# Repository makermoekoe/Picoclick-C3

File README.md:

# Picoclick-C3

</a>
</a>

The Picoclick C3 as well as its little brother (the C3T, T = tiny) are the successors of the well known [Picoclick](https://github.com/makermoekoe/Picoclick). The name is related to its new processor: the [ESP32-C3](https://www.espressif.com/sites/default/files/documentation/esp32-c3_datasheet_en.pdf) single core RISC-V 160MHz CPU.

The Picoclick is a tiny WiFi and BLE IoT button for several applications. Originally designed for smart home things, the Picoclick can also be used as an actuator for IFTTT automations or as an MQTT device. It is based on the single core ESP32-C3 RISC-V processor and therefore comes with tons of useful features.
With dimensions of only 10.5mm by 18mm, the C3T is not only the smallest one in the family of the Picoclicks, it is also the smallest device I have created so far.

The [Youtube video of the C3T](https://www.youtube.com/watch?v=t-50w3RsUlg) shows the assembly and soldering process, the optimization of the boot up time, the power measurements as well as some useful applications of the Picoclick.

Here are some specs of the Picoclick C3T:
- Dimensions are only 10.5x18mm
- Ultra low standby current due to latching circuit (no sleep mode needed)
- Single button & LED interface (WS2812 RGB LED)
- USB Type-C for charging the battery and flashing the ESP32-C3

## Update 14.07.2022: The Picoclick C3 is alive!

It's a pleasure for me to announce that the Picoclick C3 (the big brother of the C3T) is finally here! It comes with the most advanced features of my latest projects which occupies the following points:

- Optimized idle current: we're below 200nA (!!) current consumption (without battery protection) in idle state! (compared to 3µA for the C3T)
- Optimized antenna design, which will lead to a better performance and longer range.
- Optimized power latching circuit, which makes the firmware development easier. (especially with the Arduino IDE)
- Optimized battery charging circuit with separated status LED.
- Added second RTC crystal.
- Added FPC connector for connecting external hardware.
- Added embedded battery protection.
- Added boot emergency jumper.
- Same dimensions as the standard Picoclick.
- Added a nice "golden" logo ;)

### [Main documentation of the Picoclick-C3 can be found here!](https://makermoekoe.gitbook.io/picoclick-c3/)

## GPIOs

Function | GPIO C3T | GPIO C3 | Mode
-------- | -------- | -------- | --------
LED | GPIO6 | GPIO6 (CLK) + GPIO7 (SDI) | Output
Latch* | GPIO3 | ** | Output
Button | GPIO5 | GPIO5 | Input
Charge Stat. | GPIO1  | ext. LED | Input
Bat Voltage | GPIO4 | GPIO4 | Input
Bat Voltage EN | -- | GPIO3 | Output

*Enabling the LDO can be done by pressing the button of the device or turning the latch high. In most use cases, the latch GPIO should be turned on as the first task of the Picoclick. Once the task is completed the device can be powered off by turning the latch off (e.g. pulling it low).

**The Picoclick C3 doesn't need a latching GPIO because it uses the embedded flash's power supply pin as a reference. It can be depowered with putting the ESP32 in deepsleep. To reduce the power consumption of the ESP32 this function will disable the power of the embedded flash (`VDD_SPI`) which in result will depower the Picoclick itself. The deepsleep calling function is only necessary to pulling the `VDD_SPI` line low, not to use the deepsleep mode of the ESP32.

## Reducing power consumption

In order to reduce the power consumption of the Picoclick the following points can be done:

- Disable WiFi while not in use (e.g. if using LED animations only): `WiFi.mode(WIFI_OFF);`
- Reducing CPU frequency after WiFi stuff is completed (crystal is 40MHz): `setCpuFrequencyMhz(10); //reduce to 10MHz`
- Reducing brightness of the LEDs (can be done right after FastLED init): `FastLED.setBrightness(150);`

## Board overview C3T (Battery connections)

</a>

## Flashing firmware to the ESP32 (C3T)

**- Press and hold the button during the complete flashing process! Otherwise the ESP32 will be loose power and the upload process will crash!**

**- A battery or a power supply has to be applied to the battery pads (3.5v - 5.5v) in order to flash the device!**

Except the above, the Picoclick behaves like a normal development board. No need to get the ESP32 into download mode or pressing any reset button.

## Speed up boot process

**Following instructions are only needed for the C3T, not for the C3 as it doesn't use a separate latching GPIO.**

Due to the latching circuit, the button press has to be longer than the boot up time of the processor, because the first task should have been executed once the button is released. For most of the use cases of the Picoclick the first task is to toggle the latch GPIO high in order to enable power hold feature of the Picoclick. If this task haven't been executed before the button is released, the Picoclick is going to standby mode without finishing its main task.
Standard boot up time of the ESP32-C3 is almost 300ms. So the first task will be executed after these 300ms. This is far too long because a standard button press (especially with the metal buttons on the C3T) is around 100ms-200ms or even slightly below. Almost every task of the Picoclick would have been interrupted in this case (unless you press and hold the button...).
To speed up the boot process I got familiar with the ```menuconfig``` of the ESP-IDF. Actually the reason why I've switched from the Arduino framework to ESP-IDF was that I get access to all the configs of the ESP32-C3.

Things I have done so far:
- Set *Flash SPI mode* from *DIO* to *QIO* (in Serial flasher config)
- Set *Log output* from *Info* to *Warning* (in component config)
- Set *Bootloader log verbosity* from *Info* to *Warning* (in Bootloader config)
- Enable *Skip image validation from power on* (in Bootloader config)

These points result in a boot up time of around 68ms which is almost quite fantastic. The test I've done so far were quite sufficient. If it is possible to make it even faster or if you have other ideas which could lead into the right direction then please let me know!

## Power consumption C3T

These power measurements are done with the Otii Arc power analyzer and its dedicated software. The average and peak current can be seen in the top right corner and is based on the selected frame in the current graph.
The Picoclick C3T is used as an ESP-NOW slave in this case, which is probably the fastest solution of any wireless connection.

A complete Picoclick task will look like this, whereby the LED part in the end is the longest part. The whole task took about 1,7 seconds, but the transmission itself is completed after around 200ms. The other part is with disabled WiFi and only used to do some visualizations with the LED. Overall average current is below 28mA.

</a>

The ESP-NOW package is sent in the first 200ms. Average current is 73mA here.

</a>

As already said, the rest is just visualization stuff which will use 22mA of current in average.

</a>

Probably the most interesting part is the standby current, because it's the most used state of the Picoclick. As the device doesn't use any sleep mode, we're getting as low as 3µA in this state. This is only related to the battery monitoring feature. As the voltage divider between ```Vbat``` and ```GND``` is ```1MOhm + 250kOhm = 1.25MOhm``` the current flow through it is about 3µA.

</a>

## Battery for the Picoclick

### C3T

The optimal battery, which is shown in the picture below, is a 301012 LiPo battery (3.0mm thick, 10mm width, 12mm length). Nevertheless you can use whatever single cell LiPo battery you want. Charging current is set to 20mA, to be used with those 20-30mAh batteries. For larger capacity batteries the battery charging time will - of course - increase. For 20-30mAh charging time is about 1h - 1,5h.

Below are some links for those tiny batteries (no sponsor, no affiliate, just for info):

[Aliexpress 301012](https://de.aliexpress.com/item/1005003644834180.html)

[Aliexpress 401012](https://de.aliexpress.com/item/32794940086.html)

[eBay 301012](https://www.ebay.com/itm/333907143841)

</a>

### C3

As the Picoclick C3 comes with an embedded battery protection, the protection of the LiPo battery itself is redundant. Therefore you can use these tiny cells which are used by BT headsets. They come in a 401010 or 301010 package.

[Aliexpress 401010](https://de.aliexpress.com/item/1005004324462178.html)

## Flashing adapter with pogopins for the C3T

In order to flash boards without soldering wires or batteries to the Picoclick, I decided to print a simple flashing adapter which uses 1mm pogopins to make contact to the battery pads on the board. Just plug in the USB cable, shift the device in, press it down to the pogopins and hit the upload button. Simple overview is given below.

</a>
</a>

## Cases for the C3T

Round design. Combined with two M2x8mm screws.

</a>

# FAQ

## My Picoclick C3T is not shown on the device list when I plug it in the computer - what can I do?
- Your Picoclick is well tested before shipping, so it is probably not broken. Make sure you have connected a decent power supply to the battery connections (3.5v - 5.5v). Battery polarity is shown above. The USB-C jack is only for charging the battery and to flash the ESP32 - not for powering the device.

## Media

Hackster.io article by James Lewis: [Picoclick C3T Is the World's Smallest IoT Button and It Has a RISC-V Processor](https://www.hackster.io/news/picoclick-c3t-is-the-world-s-smallest-iot-button-and-it-has-a-risc-v-processor-7eddb2c14bda?fbclid=IwAR0fc_usR9xU9rvV6_ah3hptwWU2ObRKkqjKUgYzedlxkP4QRlh8Du6uMtc)

Electronics-lab.com article by Abhishek Jadhav: [Picoclick C3T IOT button built around ESP32-C3 RISC-V processor – supports WIFI and BLE](https://www.electronics-lab.com/picoclick-c3t-iot-button-built-around-esp32-c3-risc-v-processor-supports-wifi-and-ble/)

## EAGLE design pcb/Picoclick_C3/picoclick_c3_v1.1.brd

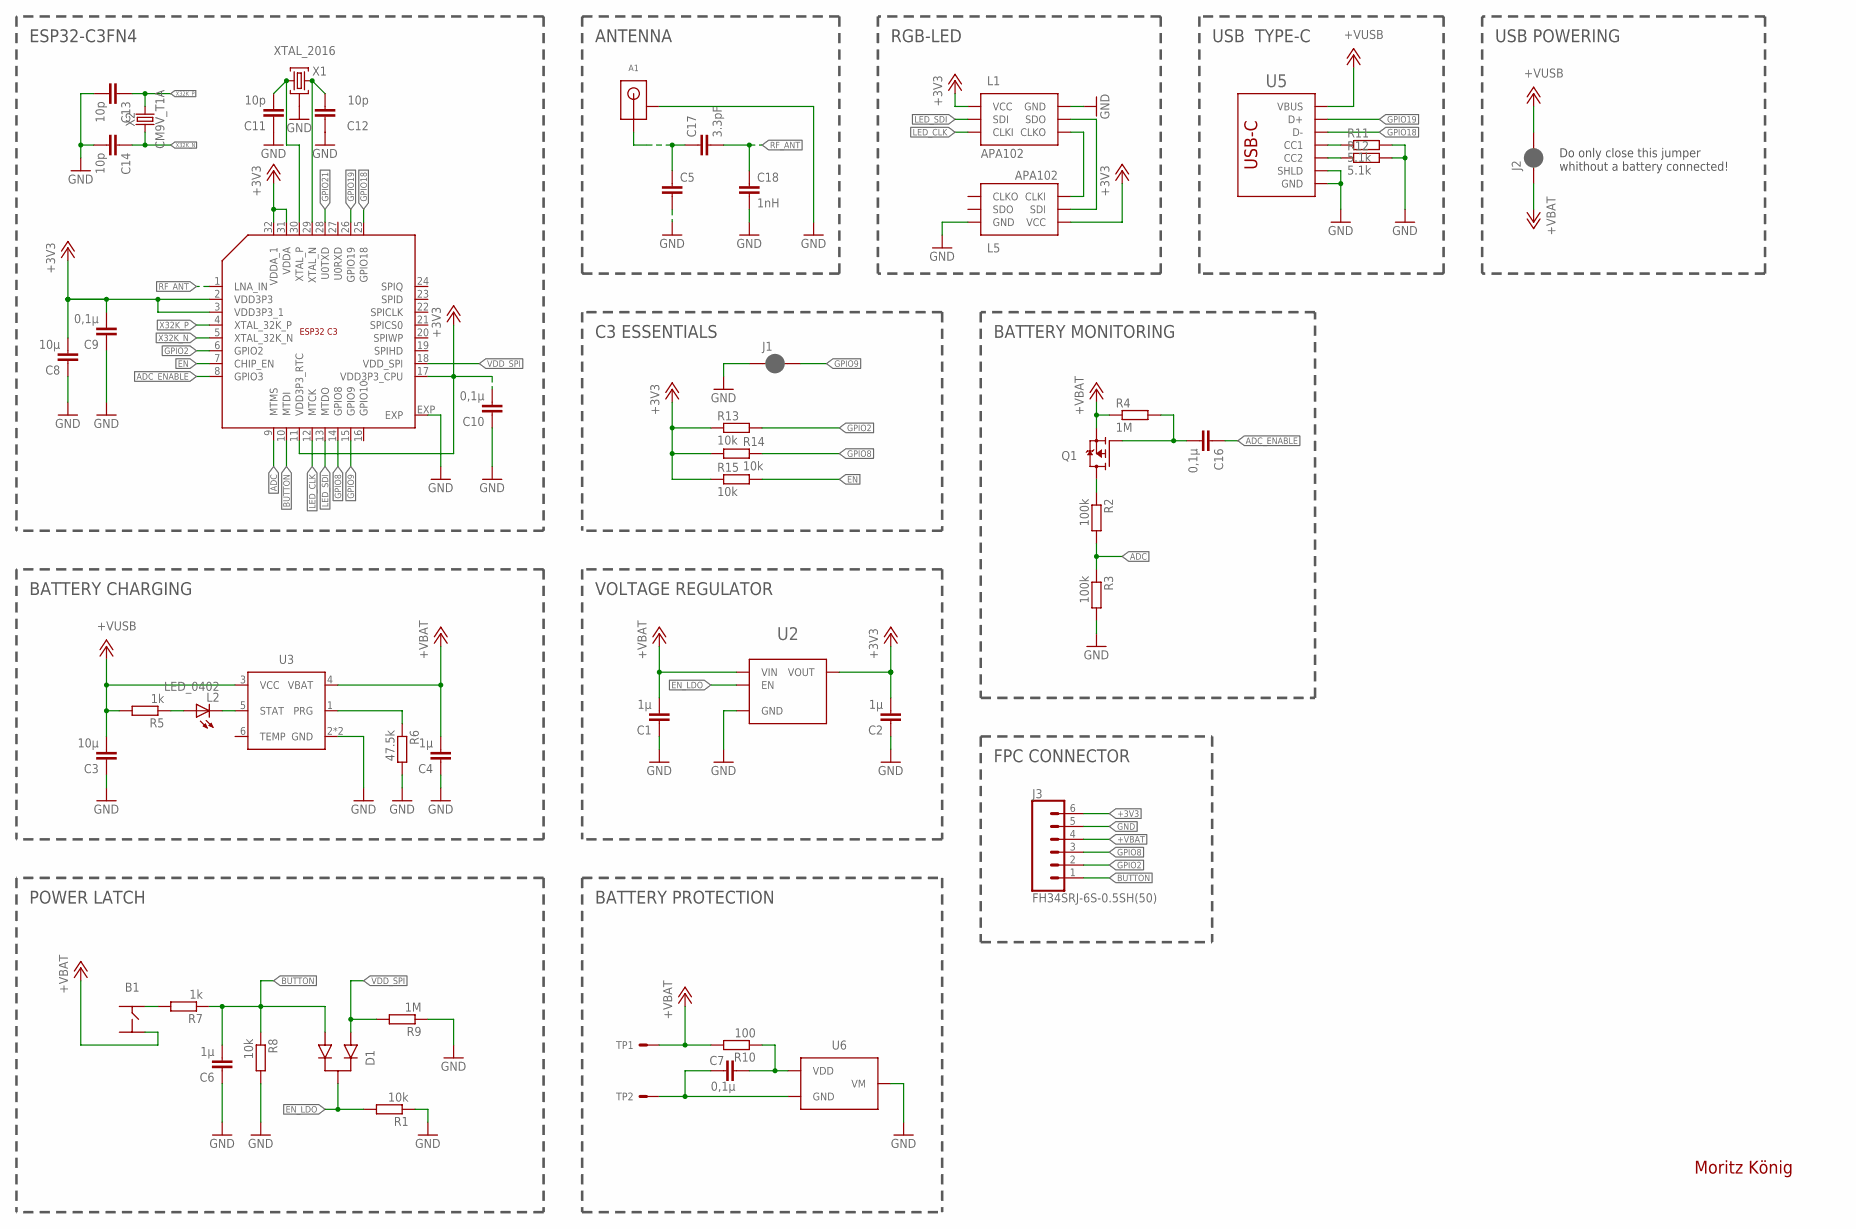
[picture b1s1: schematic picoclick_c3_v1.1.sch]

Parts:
A1: RFECA3216060A1T_NEW3_M
B1: BUTTON_4PIN; BUTTON_SMD_12MM
C1, C2, C4, C6: 1µ; C0402_S
C3, C8: 10µ; C0402_S
C5: C0402_S
C7, C9, C10, C16: 0,1µ; C0402_S
C11, C12, C13, C14: 10p; C0402_S
C17: 3.3pF; C0402_S
C18: 1nH; C0402_S
D1: DAN222; SOT523
J1: SMT_JUMPER_2_NC_PASTE; JUMPER_SMALL
J2: JUMPER_SMALL
J3: FH34SRJ-6S-0.5SH(50)
L1, L5: APA102_2020
L2: LED_0402; CHIPLED_0402
Q1: WPM2031+SOT1123; SOT723+1123
R1, R8, R13, R14, R15: 10k; R0402
R2, R3: 100k; R0402
R4, R9: 1M; R0402
R5, R7: 1k; R0402
R6: 47.5k; R0402
R10: 100; R0402
R11, R12: 5.1k; R0402
TP1, TP2: TP/SP-1.5X2.0; SOLDERPAD_1.5X2.0
U1: ESP32_C3_QFN32; QFN32
U2: MIC5504; TDFN4
U3: WS4518D; DFN-6
U5: USB_C_C393939; USBC_C393939
U6: XB6042I2SV; TDFN4
X1: XTAL_2016
X2: CM9V_T1A; XTAL_1016

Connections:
+3V3: C2.P$2 (2), C8.P$2 (2), C9.P$2 (2), C10.P$2 (2), J3.6, L1.P1 (VCC), L1.P1.1 (VCC), L5.P1 (VCC), L5.P1.1 (VCC), R13.1, R14.1, R15.1, U1.2 (VDD3P3), U1.3 (VDD3P3_1), U1.11 (VDD3P3_RTC), U1.17 (VDD3P3_CPU), U1.31 (VDDA), U1.32 (VDDA_1), U2.P1 (VOUT)
+VBAT: B1.P4 (4), C1.P$2 (2), C4.P$2 (2), J2.P$1 (1), J3.4, Q1.P$2 (S), R4.1, R10.2, TP1.1, U2.P4 (VIN), U3.4 (VBAT)
+VUSB: C3.P$2 (2), J2.P$2 (2), R5.2, U3.3 (VCC), U5.A4B9 (VBUS), U5.B4A9 (VBUS)
ADC: R2.2, R3.1, U1.9 (MTMS)
ADC_ENABLE: C16.P$1 (1), U1.8 (GPIO3)
BUTTON: C6.P$2 (2), D1.2, J3.1, R7.1, R8.1, U1.10 (MTDI)
EN: R15.2, U1.7 (CHIP_EN)
EN_LDO: D1.3, R1.2, U2.P3 (EN)
GND: A1.PGND1 (GND), A1.PGND2 (GND), C1.P$1 (1), C2.P$1 (1), C3.P$1 (1), C4.P$1 (1), C5.P$2 (2), C6.P$1 (1), C8.P$1 (1), C9.P$1 (1), C10.P$1 (1), C11.P$1 (1), C12.P$1 (1), C13.P$2 (2), C14.P$2 (2), C18.P$2 (2), J1.P$1 (1), J3.5, L1.P6 (GND), L1.P6.1 (GND), L5.P6 (GND), L5.P6.1 (GND), R1.1, R3.2, R6.2, R8.2, R9.1, R11.2, R12.2, U1.EXP, U2.EXP (GND), U2.P2 (GND), U3.2 (GND), U3.EXP (GND), U5.A1B12 (GND), U5.B1A12 (GND), U5.S1 (SHLD), U5.S2 (SHLD), U5.S3 (SHLD), U5.S4 (SHLD), U6.P4 (VM), X1.P2 (G), X1.P4 (G)
GPIO2: J3.2, R13.2, U1.6 (GPIO2)
GPIO8: J3.3, R14.2, U1.14 (GPIO8)
GPIO9: J1.P$2 (2), U1.15 (GPIO9)
GPIO18: U1.25 (GPIO18), U5.A7 (D-), U5.B7 (D-)
GPIO19: U1.26 (GPIO19), U5.A6 (D+), U5.B6 (D+)
GPIO21: U1.28 (U0TXD)
LED_CLK: L1.P5 (CLKI), U1.12 (MTCK)
LED_SDI: L1.P4 (SDI), U1.13 (MTDO)
unnamed: L1.P3 (SDO), L5.P4 (SDI)
unnamed: R6.1, U3.1 (PRG)
unnamed: R12.1, U5.B5 (CC2)
unnamed: L1.P2 (CLKO), L5.P5 (CLKI)
unnamed: R11.1, U5.A5 (CC1)
unnamed: A1.PFEED (ANT), C5.P$1 (1), C17.P$1 (1)
unnamed: C11.P$2 (2), U1.30 (XTAL_P), X1.P1 (1)
unnamed: C12.P$2 (2), U1.29 (XTAL_N), X1.P3 (2)
unnamed: B1.P2 (2), R7.2
unnamed: L2.P$2 (A), R5.1
unnamed: L2.P$1 (C), U3.5 (STAT)
unnamed: Q1.P$3 (D), R2.1
unnamed: C16.P$2 (2), Q1.P$1 (G), R4.2
unnamed: C7.P$2 (2), R10.1, U6.P1 (VDD)
unnamed: C7.P$1 (1), TP2.1, U6.EXP (GND), U6.P2 (GND), U6.P3 (GND)
RF_ANT: C17.P$2 (2), C18.P$1 (1), U1.1 (LNA_IN)
VDD_SPI: D1.1, R9.2, U1.18 (VDD_SPI)
X32K_N: C14.P$1 (1), U1.5 (XTAL_32K_N), X2.P$1 (1)
X32K_P: C13.P$1 (1), U1.4 (XTAL_32K_P), X2.P$2 (2)

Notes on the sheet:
Do only close this jumper whithout a battery connected!
Moritz König
BATTERY MONITORING
ANTENNA
USB TYPE-C
VOLTAGE REGULATOR
RGB-LED
POWER LATCH
C3 ESSENTIALS
BATTERY CHARGING
ESP32-C3FN4
BATTERY PROTECTION
USB POWERING
FPC CONNECTOR

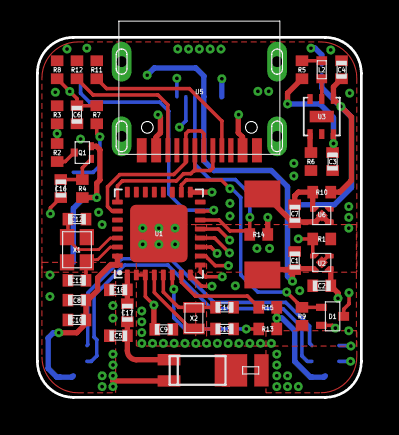
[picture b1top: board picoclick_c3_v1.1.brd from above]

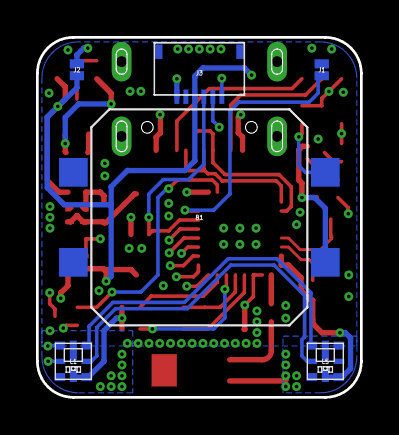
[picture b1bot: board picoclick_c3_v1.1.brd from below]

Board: 4 copper layers, 18.0 x 20.0 mm, 51 parts (6 on the bottom side), 35 nets.

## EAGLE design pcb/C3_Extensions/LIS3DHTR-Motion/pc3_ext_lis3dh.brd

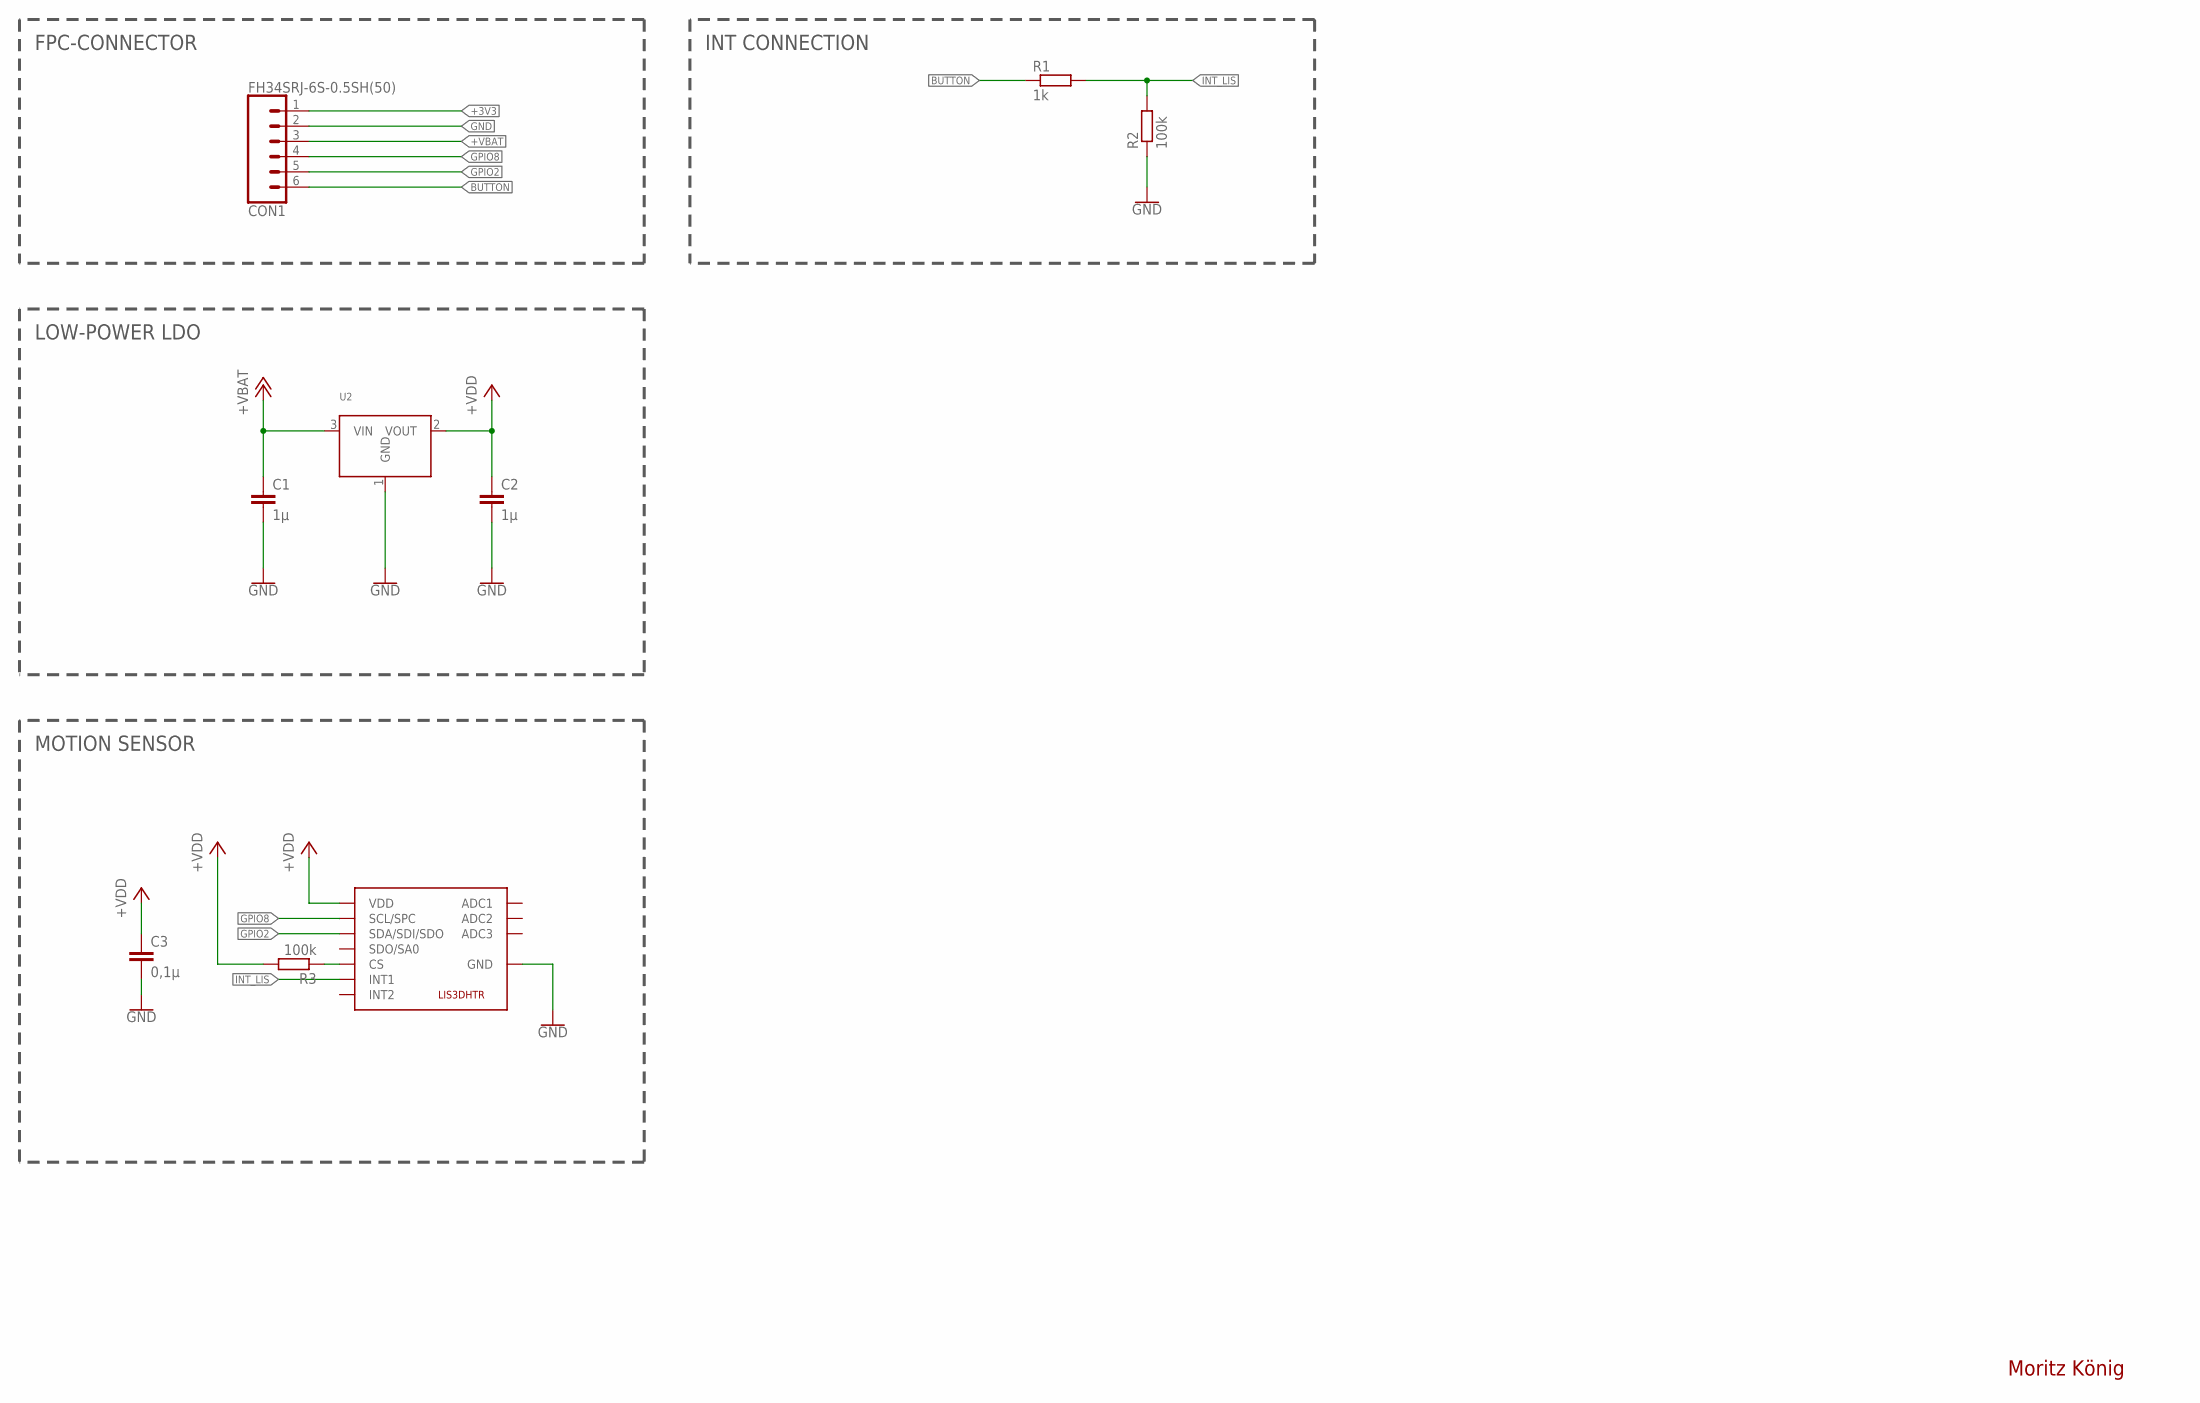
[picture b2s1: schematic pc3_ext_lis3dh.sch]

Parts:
C1, C2: 1µ; C0402_S
C3: 0,1µ; C0402_S
CON1: FH34SRJ-6S-0.5SH(50)
R1: 1k; R0402
R2, R3: 100k; R0402
U1: LIS3DHTR; LGA_16_LIS3DHTR
U2: SE82XX; SOT23-3

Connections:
+3V3: CON1.1
+VBAT: C1.P$1 (1), CON1.3, U2.3 (VIN)
+VDD: C2.P$1 (1), C3.P$1 (1), R3.2, U1.P$1 (VDD), U1.P$14 (VDD), U2.2 (VOUT)
BUTTON: CON1.6, R1.1
GND: C1.P$2 (2), C2.P$2 (2), C3.P$2 (2), CON1.2, R2.1, U1.P$5 (GND), U1.P$10 (GND), U1.P$12 (GND), U2.1 (GND)
GPIO2: CON1.5, U1.P$6 (SDA/SDI/SDO)
GPIO8: CON1.4, U1.P$4 (SCL/SPC)
INT_LIS: R1.2, R2.2, U1.P$11 (INT1)
unnamed: R3.1, U1.P$8 (CS)

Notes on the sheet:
Moritz König
FPC-CONNECTOR
LOW-POWER LDO
MOTION SENSOR
INT CONNECTION

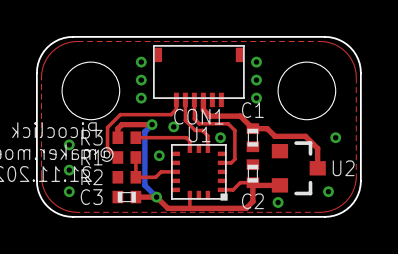
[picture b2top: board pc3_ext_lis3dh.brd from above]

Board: 2 copper layers, 18.0 x 10.0 mm, 9 parts (0 on the bottom side), 8 nets.

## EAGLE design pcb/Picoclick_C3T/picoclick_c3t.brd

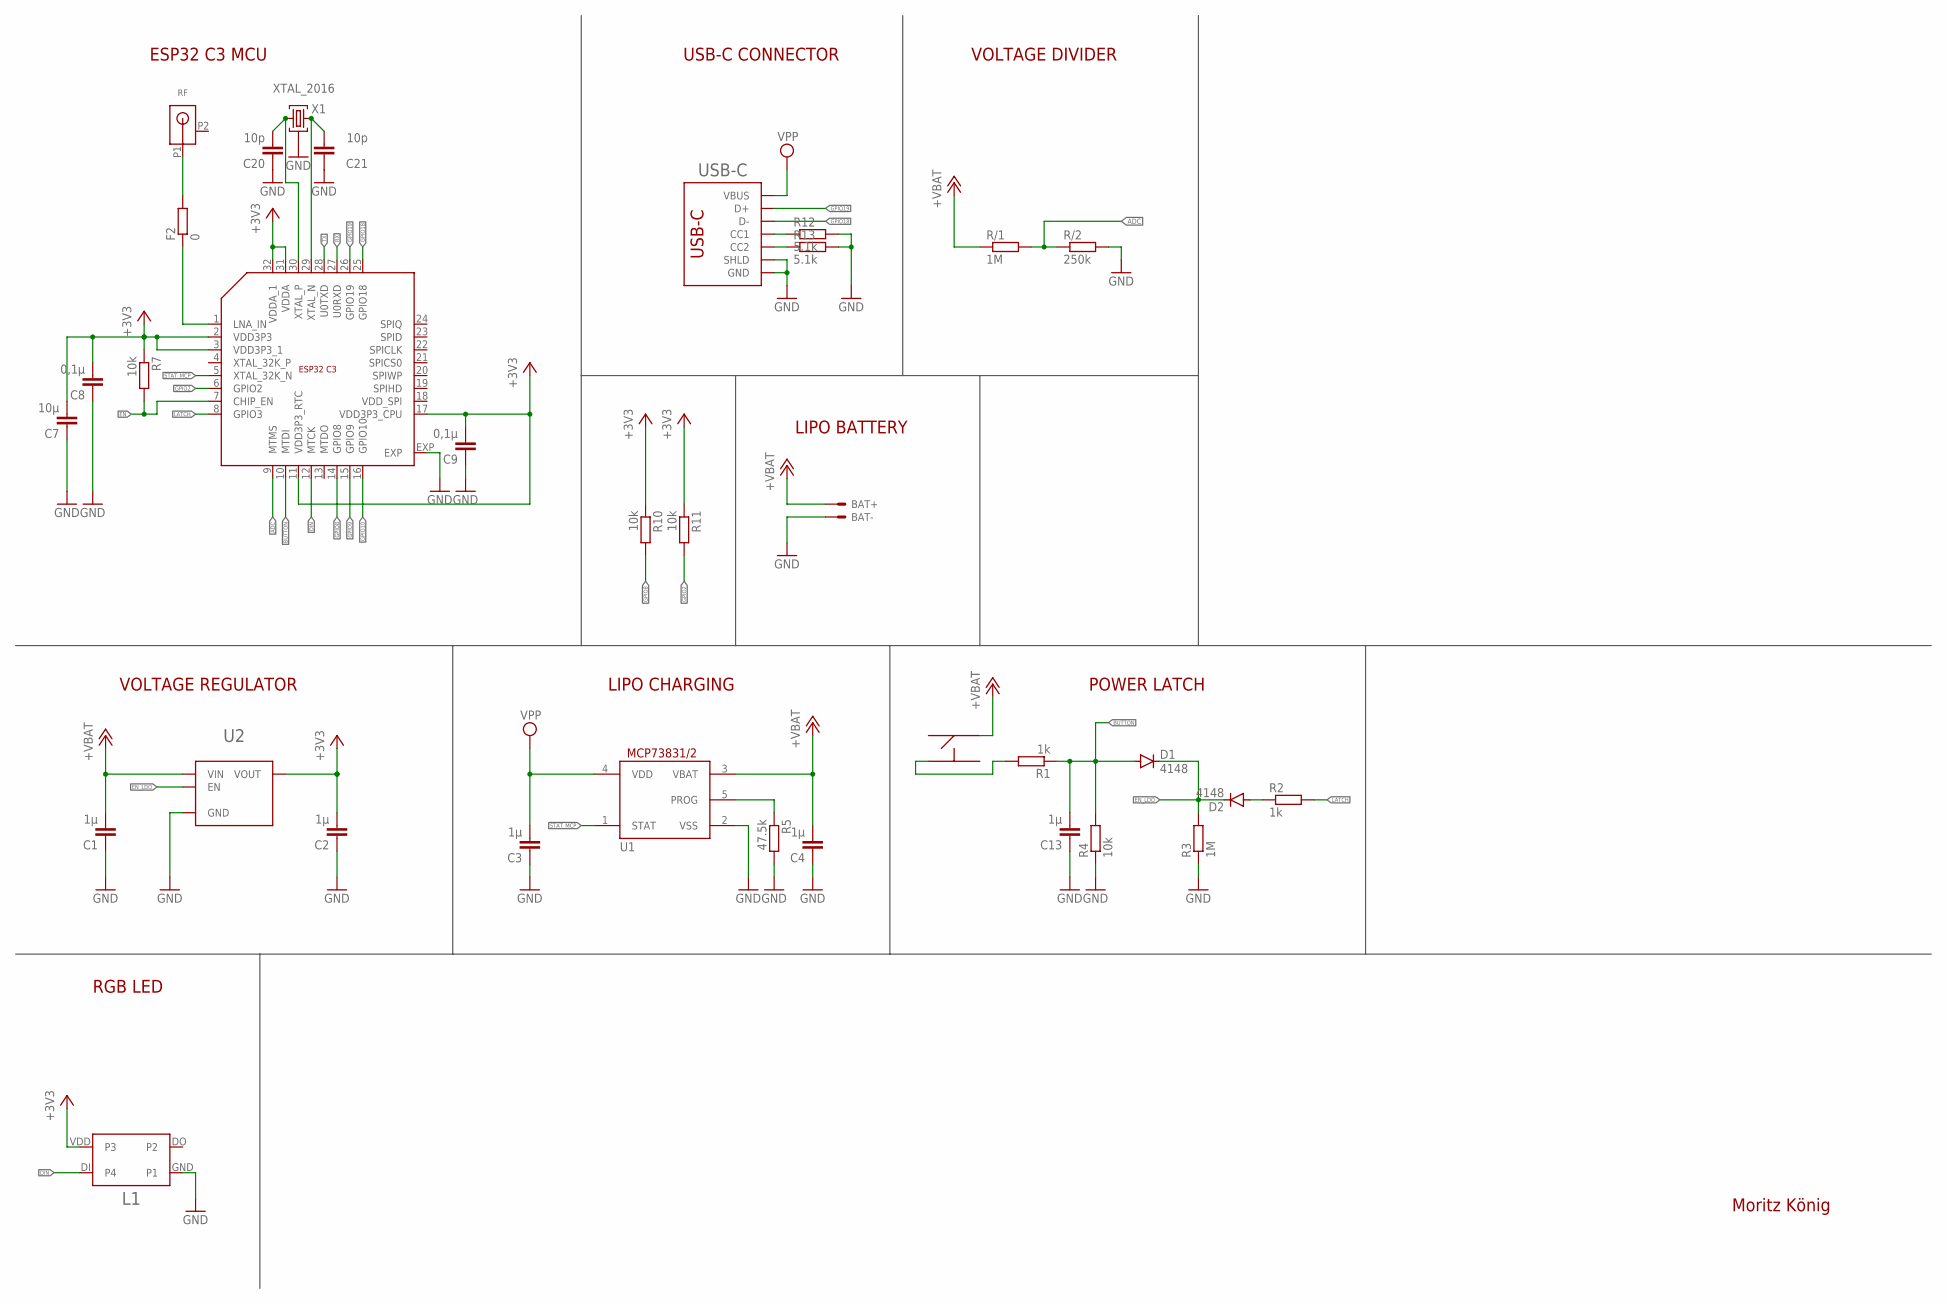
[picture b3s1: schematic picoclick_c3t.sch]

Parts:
BAT+: TP/SP-1.5X1.0; SOLDERPAD_1.5X1.0
BAT-: TP/SP-1.5X1.0; SOLDERPAD_1.5X1.0
C1, C2, C3, C4, C13: 1µ; C0402_S
C7: 10µ; C0402_S
C8, C9: 0,1µ; C0402_S
C20, C21: 10p; C0402_S
D1, D2: 4148; SOD523
ESP1: ESP32_C3_QFN32; QFN32
F2: 0; R0402
L1: WS2812_2020
R1, R2: 1k; R0402
R3: 1M; R0402
R4, R7, R10, R11: 10k; R0402
R5: 47.5k; R0402
R12, R13: 5.1k; R0402
R/1: 1M; R0402
R/2: 250k; R0402
RF: ANT3216LL00R2400A
U1: BRCL4054BME; SOT23-5
U2: MIC5504; TDFN4
U$1: BUTTON_ST-1187-3
USB-C: USB_C_C393939; USBC_C393939
X1: XTAL_2016; XTYL_2016

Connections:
+3V3: C2.P$2 (2), C7.P$2 (2), C8.P$2 (2), C9.P$2 (2), ESP1.2 (VDD3P3), ESP1.3 (VDD3P3_1), ESP1.11 (VDD3P3_RTC), ESP1.17 (VDD3P3_CPU), ESP1.31 (VDDA), ESP1.32 (VDDA_1), L1.VDD (P3), R7.1, R10.1, R11.1, U2.P1 (VOUT)
+VBAT: BAT+.1, C1.P$2 (2), C4.P$2 (2), R/1.1, U1.3 (VBAT), U2.P4 (VIN), U$1.P2
ADC: ESP1.9 (MTMS), R/1.2, R/2.1
BUTTON: C13.P$2 (2), D1.A, ESP1.10 (MTDI), R1.1, R4.2
DIN: ESP1.12 (MTCK), L1.DI (P4)
EN: ESP1.7 (CHIP_EN), R7.2
EN_LDO: D1.C, D2.C, R3.2, U2.P3 (EN)
GND: BAT-.1, C1.P$1 (1), C2.P$1 (1), C3.P$1 (1), C4.P$1 (1), C7.P$1 (1), C8.P$1 (1), C9.P$1 (1), C13.P$1 (1), C20.P$1 (1), C21.P$1 (1), ESP1.EXP, L1.GND (P1), R3.1, R4.1, R5.2, R12.2, R13.2, R/2.2, U1.2 (VSS), U2.EXP (GND), U2.P2 (GND), USB-C.A1B12 (GND), USB-C.B1A12 (GND), USB-C.S1 (SHLD), USB-C.S2 (SHLD), USB-C.S3 (SHLD), USB-C.S4 (SHLD), X1.P2 (G), X1.P4 (G)
GPIO2: ESP1.6 (GPIO2), R11.2
GPIO8: ESP1.14 (GPIO8), R10.2
GPIO9: ESP1.15 (GPIO9)
GPIO10: ESP1.16 (GPIO10)
GPIO18: ESP1.25 (GPIO18), USB-C.A7 (D-), USB-C.B7 (D-)
GPIO19: ESP1.26 (GPIO19), USB-C.A6 (D+), USB-C.B6 (D+)
LATCH: ESP1.8 (GPIO3), R2.2
unnamed: R1.2, U$1.P3
unnamed: ESP1.1 (LNA_IN), F2.1
unnamed: F2.2, RF.P1 (ANT)
unnamed: D2.A, R2.1
unnamed: R13.1, USB-C.B5 (CC2)
unnamed: R5.1, U1.5 (PROG)
unnamed: R12.1, USB-C.A5 (CC1)
unnamed: C20.P$2 (2), ESP1.30 (XTAL_P), X1.P1 (1)
unnamed: C21.P$2 (2), ESP1.29 (XTAL_N), X1.P3 (2)
RX: ESP1.27 (U0RXD)
STAT_MCP: ESP1.5 (XTAL_32K_N), U1.1 (STAT)
TX: ESP1.28 (U0TXD)
VPP: C3.P$2 (2), U1.4 (VDD), USB-C.A4B9 (VBUS), USB-C.B4A9 (VBUS)

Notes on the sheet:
Moritz König
VOLTAGE DIVIDER
LIPO CHARGING
VOLTAGE REGULATOR
POWER LATCH
RGB LED
USB-C CONNECTOR
ESP32 C3 MCU
LIPO BATTERY

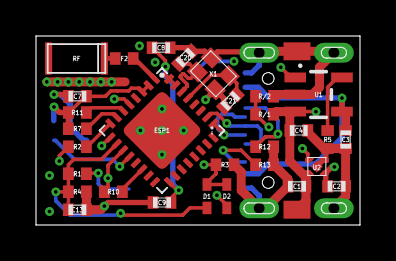
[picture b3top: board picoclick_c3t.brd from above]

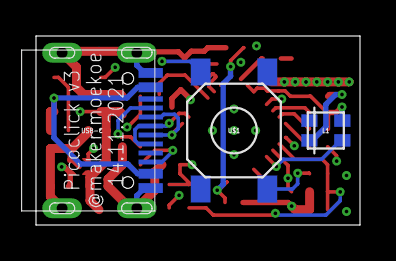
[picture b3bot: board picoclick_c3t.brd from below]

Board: 4 copper layers, 17.9 x 10.4 mm, 35 parts (3 on the bottom side), 24 nets.

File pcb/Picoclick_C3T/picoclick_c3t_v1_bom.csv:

"Part";"Value";"Device";"Package";"Description";"";
"BAT+";"TP/SP-1.5X1.0";"TP/SP-1.5X1.0";"SOLDERPAD_1.5X1.0";"Solderpads/Testpads";"";
"BAT-";"TP/SP-1.5X1.0";"TP/SP-1.5X1.0";"SOLDERPAD_1.5X1.0";"Solderpads/Testpads";"";
"C1";"1µ";"C-EU-0402-WOKEEPOUT_S";"C0402_S";"";"";
"C2";"1µ";"C-EU-0402-WOKEEPOUT_S";"C0402_S";"";"";
"C3";"1µ";"C-EU-0402-WOKEEPOUT_S";"C0402_S";"";"";
"C4";"1µ";"C-EU-0402-WOKEEPOUT_S";"C0402_S";"";"";
"C7";"10µ";"C-EU-0402-WOKEEPOUT_S";"C0402_S";"";"";
"C8";"0,1µ";"C-EU-0402-WOKEEPOUT_S";"C0402_S";"";"";
"C9";"0,1µ";"C-EU-0402-WOKEEPOUT_S";"C0402_S";"";"";
"C13";"1µ";"C-EU-0402-WOKEEPOUT_S";"C0402_S";"";"";
"C20";"10p";"C-EU-0402-WOKEEPOUT_S";"C0402_S";"";"";
"C21";"10p";"C-EU-0402-WOKEEPOUT_S";"C0402_S";"";"";
"D1";"4148";"DIODE-SOD523";"SOD523";"DIODE";"";
"D2";"4148";"DIODE-SOD523";"SOD523";"DIODE";"";
"ESP1";"ESP32_C3_QFN32";"ESP32_C3_QFN32";"QFN32";"";"";
"F2";"0";"R-EU-0402-WOKEEPOUT";"R0402";"";"";
"L1";"WS2812_2020";"WS2812_2020";"WS2812_2020";"";"";
"R/1";"1M";"R-EU-0402-WOKEEPOUT";"R0402";"";"";
"R/2";"250k";"R-EU-0402-WOKEEPOUT";"R0402";"";"";
"R1";"1k";"R-EU-0402-WOKEEPOUT";"R0402";"";"";
"R2";"1k";"R-EU-0402-WOKEEPOUT";"R0402";"";"";
"R3";"1M";"R-EU-0402-WOKEEPOUT";"R0402";"";"";
"R4";"10k";"R-EU-0402-WOKEEPOUT";"R0402";"";"";
"R5";"47.5k";"R-EU-0402-WOKEEPOUT";"R0402";"";"";
"R7";"10k";"R-EU-0402-WOKEEPOUT";"R0402";"";"";
"R10";"10k";"R-EU-0402-WOKEEPOUT";"R0402";"";"";
"R11";"10k";"R-EU-0402-WOKEEPOUT";"R0402";"";"";
"R12";"5.1k";"R-EU-0402-WOKEEPOUT";"R0402";"";"";
"R13";"5.1k";"R-EU-0402-WOKEEPOUT";"R0402";"";"";
"RF";"ANT3216LL00R2400A";"ANT3216LL00R2400A";"ANT3216LL00R2400A";"";"";
"U$1";"BUTTON_ST-1187-3";"BUTTON_ST-1187-3";"BUTTON_ST-1187-3";"";"";
"U1";" BRCL4054BME";"MCP73831_SOT23_5";"SOT23-5";"";"";
"U2";"MIC5504";"MIC5504";"TDFN4";"";"";
"USB-C";"USB_C_C393939";"USB_C_C393939";"USBC_C393939";"";"";
"X1";"XTAL_2016";"XTAL_2016";"XTYL_2016";"";"";

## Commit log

2021-12-31 initial commit, basic structure
2021-12-31 update doc
2022-01-02 added basic hardware test
    PlatformIO project with ESP-IDF
2022-01-06 added optimized boot process to docs
2022-01-09 added docs
2022-01-09 modified docs
2022-01-09 added power measurements
2022-01-09 added img
2022-01-09 added ESP-NOW example
2022-01-09 updated docs
2022-01-11 edited docs
2022-01-11 added gerbers, bom, battery info
2022-01-11 added images
2022-01-12 clean up repo; removed .DS_Store; add gitignore
2022-01-14 added PC3T 3D files
2022-01-14 uploaded case design 1
2022-01-14 added tindie link
2022-01-17 added boards description
2022-01-21 added eagle board files
2022-01-24 added optimized hardware test code
    with battery reading
2022-01-25 added pogo flasher
2022-01-25 added flashing notes
2022-01-25 added license
2022-01-26 deleted readme in code example
2022-01-28 added ESP-Now basic example
2022-01-28 removed build files from espnow example
2022-01-28 deleted first espnow example
2022-02-03 added faq to docs
2022-04-25 added pin1 markings of ldo, mcu and antenna
2022-05-12 added ESPNOW2MQTT bridge example
2022-05-22 added round case files
2022-05-22 added two versions of a keyring case
2022-05-22 removed old case top part
2022-07-08 preparation for the Picoclick-C3 release
2022-07-12 documentation for the Picoclick C3
2022-07-14 added first c3 case
2022-07-14 added board overview for the C3
2022-07-27 updated docs for extension port
2022-08-05 list all extension boards
2022-08-05 added pictures of extension boards
2022-08-08 edited description
2022-08-10 added vcnl4040 extension board
2022-08-10 added gif of picoclick c3
2022-08-10 changed height of thumbnails
2022-08-10 changed height of tn
2022-09-21 added battery monitoring description
2022-09-22 added power reducing chapter to docs
2022-10-07 added new clear case
    - more space for the battery
    - lock mechanism for bot and top
2022-10-07 added motion extension board pcb files
2022-10-14 added code examples for the C3
2022-10-24 main documentation C3 in gitbook
2022-11-15 added code examples for the extensions (expander, motion, oled)
2022-11-18 added gif with oled display
2022-11-19 added picture
2022-12-02 added cases for ext motion, oled049 and pir; add gif for expander extention
2023-01-09 added board files for the C3
2023-02-19 added 3D model PC3 PCB as step file
